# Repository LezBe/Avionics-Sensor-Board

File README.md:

# Avionics Sensor Board

Central hardware repository for the avionics team's multi-sensor PCB.

This repository is organized so team members can develop and review individual sensor circuits independently while maintaining one controlled design for the integrated sensor board.

## Goals

- Consolidate individual sensor designs in one repository
- Keep each sensor circuit modular and easy to review
- Standardize power, SPI communication, and MCU interfaces
- Maintain a controlled integrated KiCad project
- Preserve design decisions, datasheets, manufacturing files, and test results
- Make collaboration and revision history easier through Git and GitHub

## Repository Structure

```text
Avionics-Sensor-Board/
├── hardware/
│   ├── sensors/
│   │   ├── lsm6dso32/           # LSM6DSO32 IMU design/documentation
│   │   └── _template/           # Template for future sensor modules
│   ├── power/
│   ├── communications/
│   └── sensor_board/
├── libraries/
│   └── footprints/
│       └── LSM6DSO32/
├── docs/
│   ├── architecture/
│   ├── requirements/
│   ├── datasheets/
│   │   └── LSM6DSO32.md
│   └── design_reviews/
├── manufacturing/
├── testing/
└── firmware/
```

## Current Sensor Design

### LSM6DSO32 6-Axis IMU

The LSM6DSO32 is planned as the board's inertial sensor, providing 3-axis acceleration and 3-axis angular-rate measurements.

This branch contains design documentation, official ST references, SPI integration requirements, and footprint-review guidance. A KiCad schematic has not yet been created or imported.

See [hardware/sensors/lsm6dso32/README.md](hardware/sensors/lsm6dso32/README.md).

## Communication Architecture

SPI is the board-standard sensor interface.

Shared bus lines are expected to include:

- `SPI_SCK`
- `SPI_MOSI`
- `SPI_MISO`

Each SPI peripheral should have its own dedicated chip-select signal. Interrupt lines should be routed separately where required.

## Sensor Status

| Sensor / Subsystem | Function | Interface | Owner | Schematic | Integrated | Footprint Verified | Tested |
|---|---|---|---|---|---|---|---|
| LSM6DSO32 | 6-Axis IMU | SPI | TBD | Pending | No | No | No |
| Additional Sensor | TBD | SPI | TBD | Not Started | No | N/A | No |
| Power | Power Distribution | Power | TBD | Not Started | No | N/A | No |

## LSM6DSO32 References

- Sensor documentation: [hardware/sensors/lsm6dso32/](hardware/sensors/lsm6dso32/)
- Datasheet notes: [docs/datasheets/LSM6DSO32.md](docs/datasheets/LSM6DSO32.md)
- Footprint review: [libraries/footprints/LSM6DSO32/README.md](libraries/footprints/LSM6DSO32/README.md)

## Branching

Keep sensor-specific work on feature branches until it is ready for review.

See [CONTRIBUTING.md](CONTRIBUTING.md) for the team workflow.

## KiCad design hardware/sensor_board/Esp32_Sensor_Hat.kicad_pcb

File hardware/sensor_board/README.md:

# Integrated Sensor Board

This folder contains the final integrated KiCad project.

```text
sensor_board/
├── sensor_board.kicad_pro
├── sensor_board.kicad_sch
├── sensor_board.kicad_pcb
├── sensor_board.kicad_dru
└── sheets/
    ├── power.kicad_sch
    ├── sensor_1.kicad_sch
    ├── sensor_2.kicad_sch
    └── interfaces.kicad_sch
```

Use hierarchical sheets for major subsystems so multiple designers can work with fewer merge conflicts.

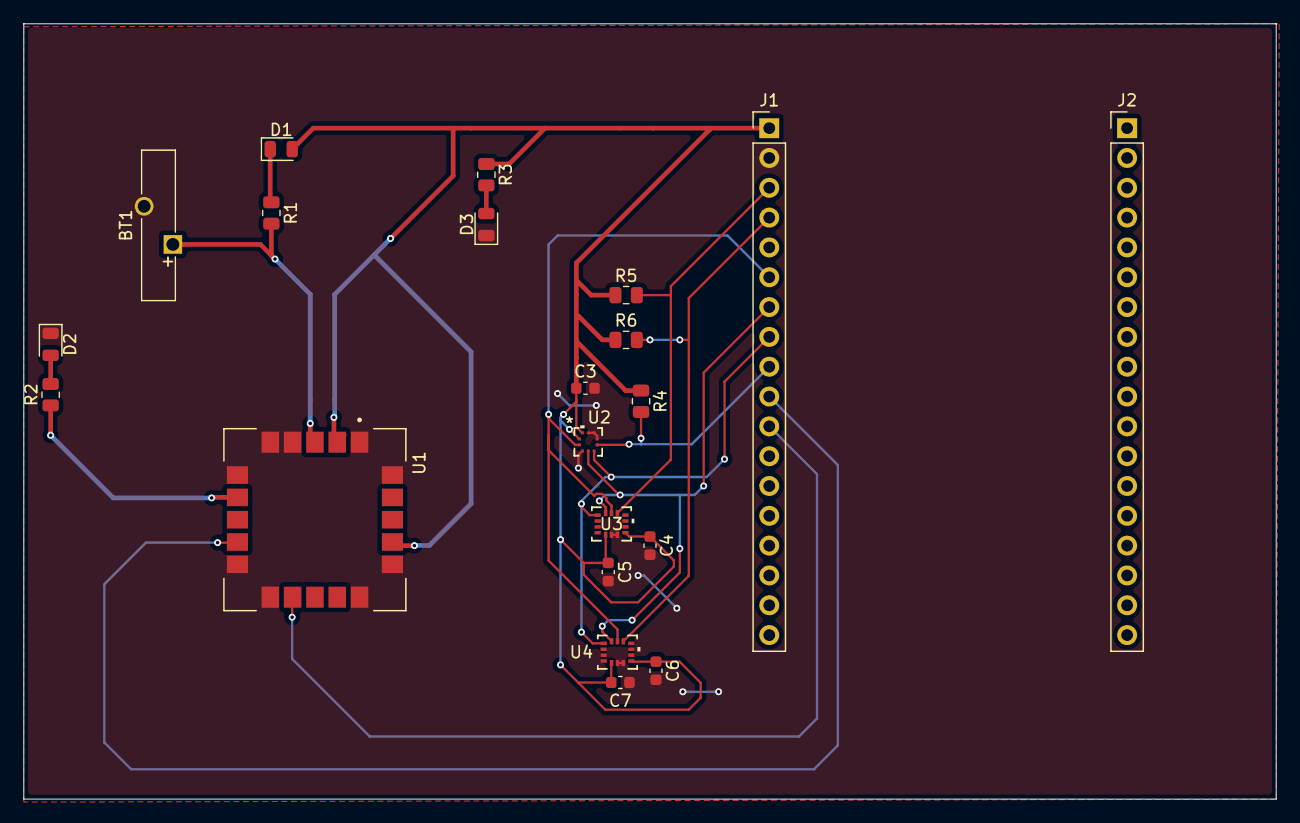
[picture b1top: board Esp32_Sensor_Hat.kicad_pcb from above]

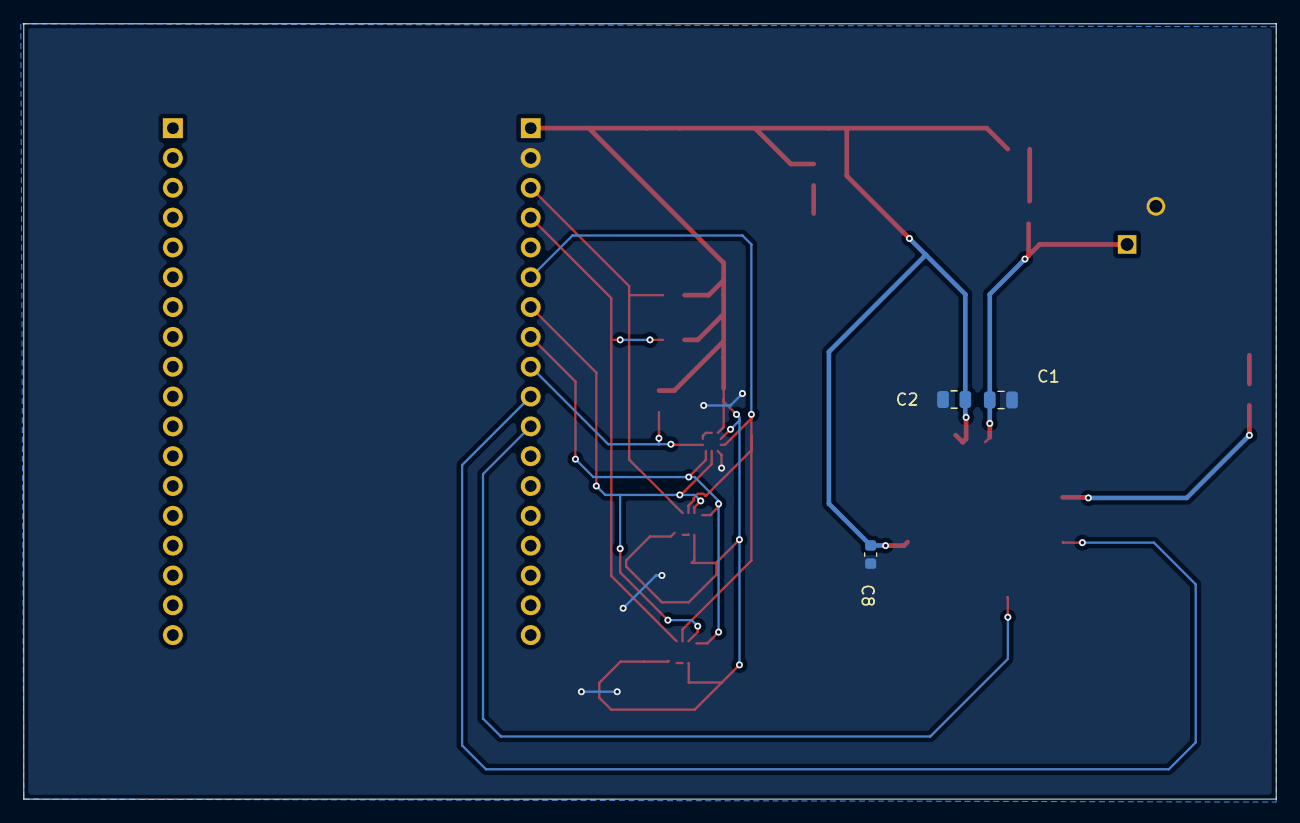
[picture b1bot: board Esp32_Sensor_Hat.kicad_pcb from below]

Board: 2 copper layers, 106.7 x 66.0 mm, 24 parts (3 on the bottom side), 15 nets.

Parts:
BT1: Battery; Battery_Panasonic_CR1220-VCN_Vertical_CircularHoles
C1, C2: 0.1uF; C_0805_2012Metric
C3: 100nF; C_0603_1608Metric
C4, C5, C6, C7: 100 nF; C_0603_1608Metric
C8: 1.0uF; C_0603_1608Metric
D1: 0.5A/40V/420mV; D_0805_2012Metric
D2, D3: LED; LED_0805_2012Metric
J1, J2: Conn_01x18_Pin; PinHeader_1x18_P2.54mm_Vertical
R1: 3.3k; R_0805_2012Metric
R2: 2.2k; R_0805_2012Metric
R3: 1k; R_0805_2012Metric
R4: 100kohm; R_0805_2012Metric
R5, R6: 10K; R_0805_2012Metric
U1: SAM-M10Q-00B; XCVR_SAM-M10Q-00B
U2: BMP581; QFN10_BMP581_BOS
U3, U4: LSM6DSO32TR; LGA_O32XTR_STM

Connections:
+3.3V: C2.1, C3.1, C4.1, C5.1, C6.1, C7.1, C8.1, D1.2 (A), J1.1, R3.1, R4.1, R5.1, R6.1, U1.2 (V_IO), U1.17 (VCC), U2.1 (VDDIO), U2.10 (VDD), U3.5 (VDDIO), U3.8 (VDD), U4.5 (VDDIO), U4.8 (VDD)
BMP_CS: J1.9, R4.2, U2.6 (CSB)
Backup: BT1.1 (+), C1.1, R1.2, U1.3 (V_BCKP)
GND: BT1.2 (-), C1.2, C2.2, C3.2, C4.2, C5.2, C6.2, C7.2, C8.2, D2.1 (K), D3.1 (K), J1.2, U1.1 (GND), U1.4 (GND__1), U1.5 (GND__2), U1.6 (GND__3), U1.10 (GND__4), U1.11 (GND__5), U1.15 (GND__6), U1.16 (GND__7), U1.20 (GND__8), U2.3 (VSS), U2.7 (INT), U2.8 (VSS), U2.9 (VSS), U3.6 (GND), U3.7 (GND), U4.6 (GND), U4.7 (GND)
I2C_SCL: J1.11, U1.12 (SCL)
I2C_SDA: J1.10, U1.9 (SDA)
LSM_CS: J1.3, R5.2, U3.12 (CS)
LSM_CS_2: J1.4, R6.2, U4.12 (CS)
MISO: J1.8, U2.5 (SDO), U3.1 (SDO/SA0), U4.1 (SDO/SA0)
MOSI: J1.7, U2.4 (SDI), U3.14 (SDA), U4.14 (SDA)
unnamed: D1.1 (K), R1.1
unnamed: D2.2 (A), R2.2
unnamed: D3.2 (A), R3.2
PPS: R2.1, U1.7 (TIMEPULSE)
SPI_SCLK: J1.6, U2.2 (SCK), U3.13 (SCL), U4.13 (SCL)
